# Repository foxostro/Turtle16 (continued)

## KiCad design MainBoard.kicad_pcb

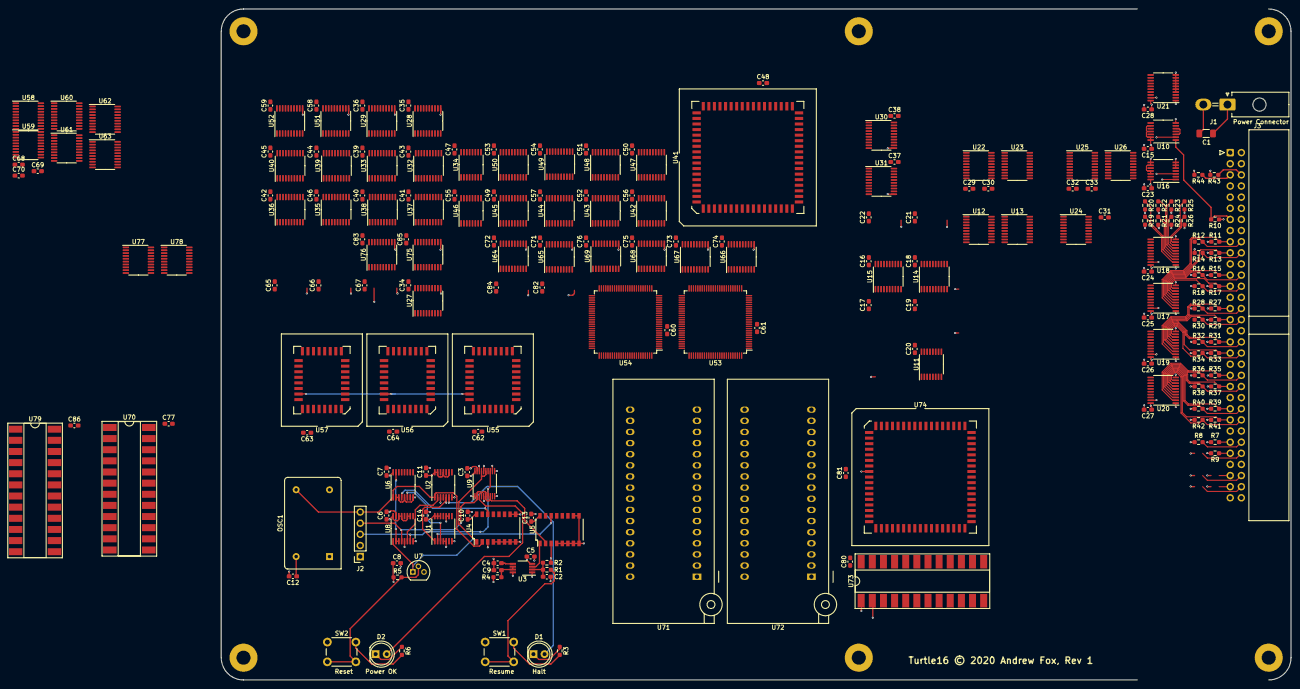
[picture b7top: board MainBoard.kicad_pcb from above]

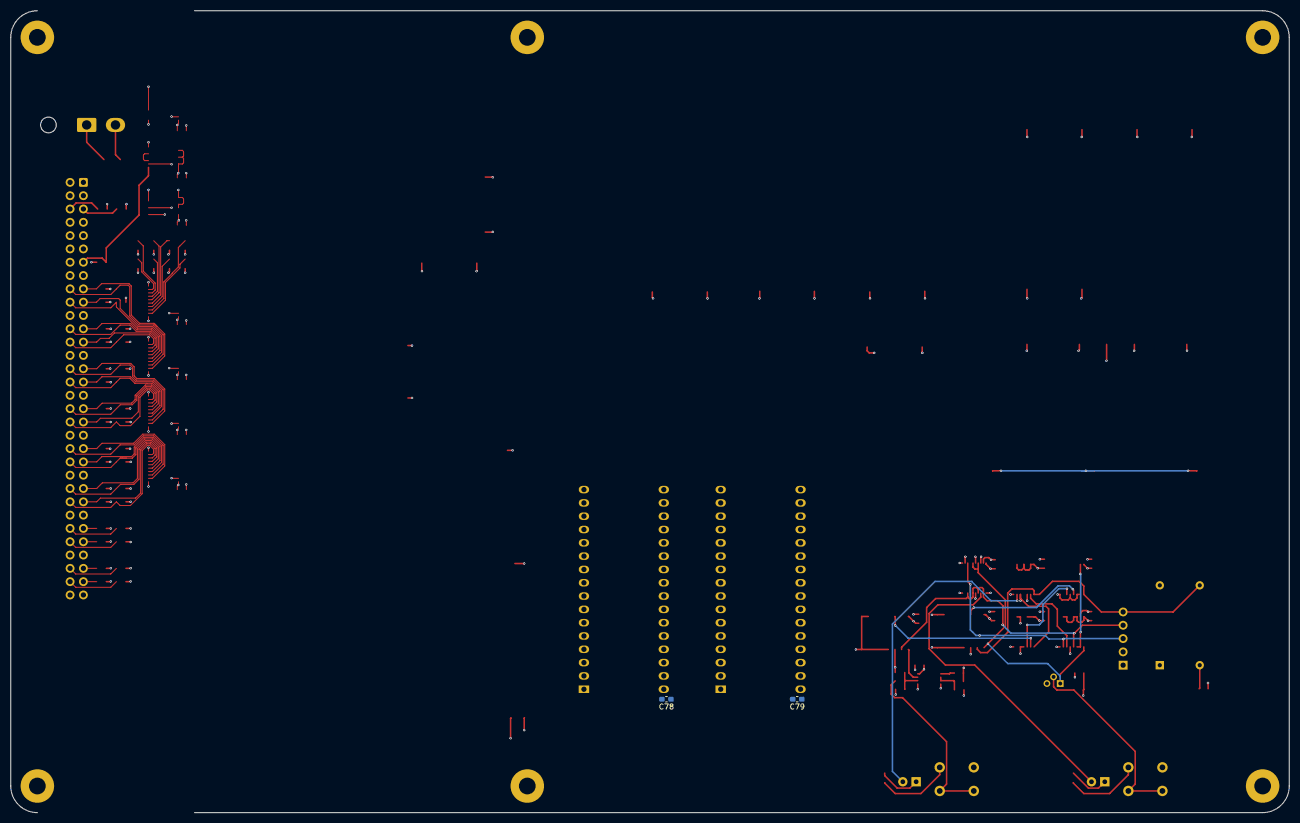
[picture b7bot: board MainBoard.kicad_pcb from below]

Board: 6 copper layers, 244.0 x 153.0 mm, 223 parts (2 on the bottom side), 442 nets.

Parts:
C1: 100µF; C_1206_3216Metric_Pad1.33x1.80mm_HandSolder
C2: 10uF; C_0603_1608Metric_Pad1.08x0.95mm_HandSolder
C3, C5, C6, C7, C8, C10, C11, C12, C13, C14, C15, C16, C17, C18, C19, C20, C21, C22, C23, C24, C25, C26, C27, C28, C29, C30, C31, C32, C33, C34, C35, C36, C37, C38, C39, C40, C41, C42, C43, C44, C45, C46, C47, C48, C49, C50, C51, C52, C53, C54, C55, C56, C57, C58, C59, C60, C61, C62, C63, C64, C65, C66, C67, C68, C69, C70, C71, C72, C73, C74, C75, C76, C77, C78, C79, C80, C81, C82, C83, C84, C85, C86: 100nF; C_0603_1608Metric_Pad1.08x0.95mm_HandSolder
C4: 0.01uF; C_0603_1608Metric_Pad1.08x0.95mm_HandSolder
C9: 22pF; C_0603_1608Metric_Pad1.08x0.95mm_HandSolder
D1: Halt; LED_D5.0mm
D2: Power OK; LED_D5.0mm
H1, H2, H3, H4, H5, H6: MountingHole_Pad; MountingHole_3.2mm_M3_Pad
J1: Power Connector; Molex_Mini-Fit_Jr_5569-02A2_2x01_P4.20mm_Horizontal
J2: External Clock; PinSocket_1x05_P2.54mm_Vertical
J3: 71922-264LF; IDC-Header_2x32_P2.54mm_Horizontal
OSC1: 12MHz; Oscillator_DIP-14
R1, R4, R5: 1kΩ; R_0603_1608Metric_Pad0.98x0.95mm_HandSolder
R2, R7, R8, R9, R10, R11, R12, R13, R14, R15, R16, R17, R18, R19, R20, R21, R22, R23, R24, R25, R26, R27, R28, R29, R30, R31, R32, R33, R34, R35, R36, R37, R38, R39, R40, R41, R42, R43, R44: 10kΩ; R_0603_1608Metric_Pad0.98x0.95mm_HandSolder
R3, R6: 220Ω; R_0603_1608Metric_Pad0.98x0.95mm_HandSolder
SW1: Resume; SW_PUSH_6mm_H5mm
SW2: Reset; SW_PUSH_6mm_H5mm
U1: 74AHCT32; TSSOP-14_4.4x5mm_P0.65mm
U2, U10: 74AHCT04; TSSOP-14_4.4x5mm_P0.65mm
U3: LM555; VSSOP-8_3.0x3.0mm_P0.65mm
U4, U5: 74F161; SOP-16_4.4x10.4mm_P1.27mm
U6, U11, U34, U46: 74AHCT138; TSSOP-16_4.4x5mm_P0.65mm
U7: MCP100-450D; TO-92
U8: 74AHCT157; TSSOP-16_4.4x5mm_P0.65mm
U9: 74AHCT244; TSSOP-20_4.4x5mm_P0.5mm
U12, U13, U14, U15, U32, U33, U35, U36, U37, U38, U39, U40, U42, U43, U44, U45, U47, U48, U49, U50: 74ABT245; TSSOP-20_4.4x6.5mm_P0.65mm
U16: 74AHCT02; TSSOP-14_4.4x5mm_P0.65mm
U17, U18, U19, U20, U21: 74AHCT245; TSSOP-20_4.4x6.5mm_P0.65mm
U22, U23, U24, U25, U26: 74ABT574; TSSOP-20_4.4x6.5mm_P0.65mm
U27: 74ABT377; TSSOP-20_4.4x6.5mm_P0.65mm
U28, U29, U30, U31, U51, U52, U64, U65, U66, U67, U68, U69, U75, U76: 74AHCT574; TSSOP-20_4.4x6.5mm_P0.65mm
U41, U74: IDT7381; PLCC-68_SMD-Socket
U53, U54: IDT7024L15PFG; TQFP-100_14x14mm_P0.5mm
U55, U56, U57: SST39SF010A-45-4I-NHE; PLCC-32_SMD-Socket
U58, U59, U60, U77, U78: 74AHCT273; TSSOP-20_4.4x6.5mm_P0.65mm
U61, U62, U63: 74AHCT240; TSSOP-20_4.4x6.5mm_P0.65mm
U70, U73, U79: ATF22V10C-7PX; DIP-24_W8.89mm_SMDSocket_LongPads
U71, U72: SST39SF010A-45-4I-NHE; DIP_Socket-32_W11.9_W12.7_W15.24_W17.78_W18.5_3M_232-1285-0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

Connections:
/Clock/Phi1: J2.4, U5.2, U8.4, U9.2, U9.4, U9.6, U9.8
/Clock/RawClockSignal: J2.5, OSC1.8, U2.1, U4.2, U6.1
/Clock/~HLT: U1.1, U2.5, U61.18
/Clock/~RDY: U4.3, U10.2, U16.3, U19.19, U20.19, U21.19
/EX/ALU/C16: U27.3, U41.20
/EX/ALU/OVF: U27.7, U41.24
/EX/ALU/RightOp0: U41.53, U42.18, U44.18, U47.18, U49.18
/EX/ALU/RightOp1: U41.54, U42.17, U44.17, U47.17, U49.17
/EX/ALU/RightOp2: U41.55, U42.16, U44.16, U47.16, U49.16
/EX/ALU/RightOp3: U41.56, U42.15, U44.15, U47.15, U49.15
/EX/ALU/RightOp4: U41.57, U42.14, U44.14, U47.14, U49.14
/EX/ALU/RightOp5: U41.58, U42.13, U44.13, U47.13, U49.13
/EX/ALU/RightOp6: U41.59, U42.12, U44.12, U47.12, U49.12
/EX/ALU/RightOp7: U41.60, U42.11, U44.11, U47.11, U49.11
/EX/ALU/RightOp8: U41.61, U43.18, U45.18, U48.18, U50.18
/EX/ALU/RightOp9: U41.62, U43.17, U45.17, U48.17, U50.17
/EX/ALU/RightOp10: U41.63, U43.16, U45.16, U48.16, U50.16
/EX/ALU/RightOp11: U41.64, U43.15, U45.15, U48.15, U50.15
/EX/ALU/RightOp12: U41.65, U43.14, U45.14, U48.14, U50.14
/EX/ALU/RightOp13: U41.66, U43.13, U45.13, U48.13, U50.13
/EX/ALU/RightOp14: U41.67, U43.12, U45.12, U48.12, U50.12
/EX/ALU/RightOp15: U41.68, U43.11, U45.11, U48.11, U50.11
/EX/ALU/Y_EX0: U30.2, U41.43, U74.53
/EX/ALU/Y_EX1: U30.3, U41.42, U74.54
/EX/ALU/Y_EX2: U30.4, U41.41, U74.55
/EX/ALU/Y_EX3: U30.5, U41.40, U74.56
/EX/ALU/Y_EX4: U30.6, U41.39, U74.57
/EX/ALU/Y_EX5: U30.7, U41.38, U74.58
/EX/ALU/Y_EX6: U30.8, U41.37, U74.59
/EX/ALU/Y_EX7: U30.9, U41.36, U74.60
/EX/ALU/Y_EX8: U31.2, U41.35, U74.61
/EX/ALU/Y_EX9: U31.3, U41.34, U74.62
/EX/ALU/Y_EX10: U31.4, U41.33, U74.63
/EX/ALU/Y_EX11: U31.5, U41.32, U74.64
/EX/ALU/Y_EX12: U31.6, U41.31, U74.65
/EX/ALU/Y_EX13: U31.7, U41.30, U74.66
/EX/ALU/Y_EX14: U31.8, U41.29, U74.67
/EX/ALU/Y_EX15: U31.9, U41.28, U74.68
/EX/ALU/Z: U27.4, U41.23
/EX/Carry: U27.2, U55.7, U56.7, U57.7
/EX/Ctl_EX1: U34.1, U61.16
/EX/Ctl_EX2: U34.2, U61.14
/EX/Ctl_EX3: U46.1, U61.12
/EX/Ctl_EX4: U46.2, U61.9
/EX/Ctl_EX5: U27.1, U61.7, U70.2
/EX/Ctl_EX6: U41.44, U61.5
/EX/Ctl_EX7: U41.45, U61.3
/EX/Ctl_EX8: U41.46, U62.18
/EX/Ctl_EX9: U41.47, U62.16
/EX/Ctl_EX10: U41.48, U62.14
/EX/Ctl_EX11: U41.49, U62.12
/EX/OVF: U27.6, U55.5, U56.5, U57.5
/EX/Select Right Operand/B0: U32.2, U42.2, U68.19
/EX/Select Right Operand/B1: U32.3, U42.3, U68.18
/EX/Select Right Operand/B2: U32.4, U42.4, U68.17
/EX/Select Right Operand/B3: U32.5, U42.5, U68.16
/EX/Select Right Operand/B4: U32.6, U42.6, U68.15
/EX/Select Right Operand/B5: U32.7, U42.7, U68.14
/EX/Select Right Operand/B6: U32.8, U42.8, U68.13
/EX/Select Right Operand/B7: U32.9, U42.9, U68.12
/EX/Select Right Operand/B8: U33.2, U35.2, U43.2, U69.19
/EX/Select Right Operand/B9: U33.3, U35.3, U43.3, U69.18
/EX/Select Right Operand/B10: U33.4, U35.4, U43.4, U69.17
/EX/Select Right Operand/B11: U33.5, U35.5, U43.5, U69.16
/EX/Select Right Operand/B12: U33.6, U35.6, U43.6, U69.15
/EX/Select Right Operand/B13: U33.7, U35.7, U43.7, U69.14
/EX/Select Right Operand/B14: U33.8, U35.8, U43.8, U69.13
/EX/Select Right Operand/B15: U33.9, U35.9, U43.9, U69.12
/EX/Select Right Operand/Ins_EX0: U39.2, U44.2, U47.2, U49.2, U64.19
/EX/Select Right Operand/Ins_EX1: U39.3, U44.3, U47.3, U49.3, U64.18
/EX/Select Right Operand/Ins_EX2: U39.4, U44.4, U49.4, U64.17
/EX/Select Right Operand/Ins_EX3: U39.5, U44.5, U49.5, U64.16
/EX/Select Right Operand/Ins_EX4: U39.6, U44.6, U44.7, U44.8, U44.9, U45.2, U45.3, U45.4, U45.5, U45.6, U45.7, U45.8, U45.9, U49.6, U64.15
/EX/Select Right Operand/Ins_EX8: U29.2, U47.4, U49.7, U65.19, U70.18
/EX/Select Right Operand/Ins_EX9: U29.3, U47.5, U49.8, U65.18, U70.17
/EX/Select Right Operand/Ins_EX10: U29.4, U47.6, U47.7, U47.8, U47.9, U48.2, U48.3, U48.4, U48.5, U48.6, U48.7, U48.8, U48.9, U49.9, U50.2, U50.3, U50.4, U50.5, U50.6, U50.7, U50.8, U50.9, U65.17, U70.16
/EX/Z: U27.5, U55.6, U56.6, U57.6
/EX/sheet5FD8D6EA/StoreOp_EX0: U32.18, U35.18, U37.18, U39.18, U51.2
/EX/sheet5FD8D6EA/StoreOp_EX1: U32.17, U35.17, U37.17, U39.17, U51.3
/EX/sheet5FD8D6EA/StoreOp_EX2: U32.16, U35.16, U37.16, U39.16, U51.4
/EX/sheet5FD8D6EA/StoreOp_EX3: U32.15, U35.15, U37.15, U39.15, U51.5
/EX/sheet5FD8D6EA/StoreOp_EX4: U32.14, U35.14, U37.14, U39.14, U51.6
/EX/sheet5FD8D6EA/StoreOp_EX5: U32.13, U35.13, U37.13, U39.13, U51.7
/EX/sheet5FD8D6EA/StoreOp_EX6: U32.12, U35.12, U37.12, U39.12, U51.8
/EX/sheet5FD8D6EA/StoreOp_EX7: U32.11, U35.11, U37.11, U39.11, U51.9
/EX/sheet5FD8D6EA/StoreOp_EX8: U33.18, U36.18, U38.18, U40.18, U52.2
/EX/sheet5FD8D6EA/StoreOp_EX9: U33.17, U36.17, U38.17, U40.17, U52.3
/EX/sheet5FD8D6EA/StoreOp_EX10: U33.16, U36.16, U38.16, U40.16, U52.4
/EX/sheet5FD8D6EA/StoreOp_EX11: U33.15, U36.15, U38.15, U40.15, U52.5
/EX/sheet5FD8D6EA/StoreOp_EX12: U33.14, U36.14, U38.14, U40.14, U52.6
/EX/sheet5FD8D6EA/StoreOp_EX13: U33.13, U36.13, U38.13, U40.13, U52.7
/EX/sheet5FD8D6EA/StoreOp_EX14: U33.12, U36.12, U38.12, U40.12, U52.8
/EX/sheet5FD8D6EA/StoreOp_EX15: U33.11, U36.11, U38.11, U40.11, U52.9
/EX/sheet5FD8D6EA/StoreOp_MEM0: U17.18, U51.19
/EX/sheet5FD8D6EA/StoreOp_MEM1: U17.17, U51.18
/EX/sheet5FD8D6EA/StoreOp_MEM2: U17.16, U51.17
/EX/sheet5FD8D6EA/StoreOp_MEM3: U17.15, U51.16
/EX/sheet5FD8D6EA/StoreOp_MEM4: U17.14, U51.15
/EX/sheet5FD8D6EA/StoreOp_MEM5: U17.13, U51.14
/EX/sheet5FD8D6EA/StoreOp_MEM6: U17.12, U51.13
/EX/sheet5FD8D6EA/StoreOp_MEM7: U17.11, U51.12
/EX/sheet5FD8D6EA/StoreOp_MEM8: U18.18, U52.19
/EX/sheet5FD8D6EA/StoreOp_MEM9: U18.17, U52.18
/EX/sheet5FD8D6EA/StoreOp_MEM10: U18.16, U52.17
/EX/sheet5FD8D6EA/StoreOp_MEM11: U18.15, U52.16
/EX/sheet5FD8D6EA/StoreOp_MEM12: U18.14, U52.15
/EX/sheet5FD8D6EA/StoreOp_MEM13: U18.13, U52.14
/EX/sheet5FD8D6EA/StoreOp_MEM14: U18.12, U52.13
/EX/sheet5FD8D6EA/StoreOp_MEM15: U18.11, U52.12
/EX/sheet5FD8D6EB/Ctl_EX14: U28.2, U62.5
/EX/sheet5FD8D6EB/Ctl_EX15: U28.3, U62.3
/EX/sheet5FD8D6EB/Ctl_EX16: U28.4, U63.18
/EX/sheet5FD8D6EB/Ctl_EX17: U28.5, U63.16
/EX/sheet5FD8D6EB/Ctl_EX18: U28.6, U63.14
/EX/sheet5FD8D6EB/Ctl_EX19: U28.7, U63.12
/EX/sheet5FD8D6EB/Ctl_EX20: U28.8, U63.9, U70.3
/EX/sheet5FD8D6EB/Ctl_MEM17: U24.2, U28.16
/EX/sheet5FD8D6EB/Ctl_MEM18: U24.3, U28.15
/EX/sheet5FD8D6EB/Ctl_MEM19: U24.4, U28.14
/EX/sheet5FD8D6EB/Ctl_MEM20: U24.5, U28.13, U70.4
/EX/sheet5FD8D6EB/SelC_MEM0: U24.7, U29.19, U70.15
/EX/sheet5FD8D6EB/SelC_MEM1: U24.8, U29.18, U70.14
/EX/sheet5FD8D6EB/SelC_MEM2: U24.9, U29.17, U70.13
/EX/sheet5FD8D6EC/Y_MEM0: U19.18, U25.2, U30.19
/EX/sheet5FD8D6EC/Y_MEM1: U19.17, U25.3, U30.18
/EX/sheet5FD8D6EC/Y_MEM2: U19.16, U25.4, U30.17
/EX/sheet5FD8D6EC/Y_MEM3: U19.15, U25.5, U30.16
/EX/sheet5FD8D6EC/Y_MEM4: U19.14, U25.6, U30.15
/EX/sheet5FD8D6EC/Y_MEM5: U19.13, U25.7, U30.14
/EX/sheet5FD8D6EC/Y_MEM6: U19.12, U25.8, U30.13
/EX/sheet5FD8D6EC/Y_MEM7: U19.11, U25.9, U30.12
/EX/sheet5FD8D6EC/Y_MEM8: U20.18, U26.2, U31.19
/EX/sheet5FD8D6EC/Y_MEM9: U20.17, U26.3, U31.18
/EX/sheet5FD8D6EC/Y_MEM10: U20.16, U26.4, U31.17
/EX/sheet5FD8D6EC/Y_MEM11: U20.15, U26.5, U31.16
/EX/sheet5FD8D6EC/Y_MEM12: U20.14, U26.6, U31.15
/EX/sheet5FD8D6EC/Y_MEM13: U20.13, U26.7, U31.14
/EX/sheet5FD8D6EC/Y_MEM14: U20.12, U26.8, U31.13
/EX/sheet5FD8D6EC/Y_MEM15: U20.11, U26.9, U31.12
/EX/sheet5FDDE432/Ins_EX5: U39.7, U64.14
/EX/sheet5FDDE432/Ins_EX6: U39.8, U64.13
/EX/sheet5FDDE432/Ins_EX7: U39.9, U40.2, U40.3, U40.4, U40.5, U40.6, U40.7, U40.8, U40.9, U64.12
/EX/sheet5FDDE432/PC_EX0: U37.2, U75.19
/EX/sheet5FDDE432/PC_EX1: U37.3, U75.18
/EX/sheet5FDDE432/PC_EX2: U37.4, U75.17
/EX/sheet5FDDE432/PC_EX3: U37.5, U75.16
/EX/sheet5FDDE432/PC_EX4: U37.6, U75.15
/EX/sheet5FDDE432/PC_EX5: U37.7, U75.14
/EX/sheet5FDDE432/PC_EX6: U37.8, U75.13
/EX/sheet5FDDE432/PC_EX7: U37.9, U75.12
/EX/sheet5FDDE432/PC_EX8: U38.2, U76.19
/EX/sheet5FDDE432/PC_EX9: U38.3, U76.18
/EX/sheet5FDDE432/PC_EX10: U38.4, U76.17
/EX/sheet5FDDE432/PC_EX11: U38.5, U76.16
/EX/sheet5FDDE432/PC_EX12: U38.6, U76.15
/EX/sheet5FDDE432/PC_EX13: U38.7, U76.14
/EX/sheet5FDDE432/PC_EX14: U38.8, U76.13
/EX/sheet5FDDE432/PC_EX15: U38.9, U76.12
/EX/~J: U62.9, U70.11, U73.3
/EX/~JABS: U62.7, U73.4
/ID/Hazard Control/FlagsNeeded: U70.1, U79.23
/ID/Hazard Control/Ins_ID11: U55.12, U56.12, U57.12, U78.9, U79.1
/ID/Hazard Control/Ins_ID12: U55.11, U56.11, U57.11, U78.12, U79.2
/ID/Hazard Control/Ins_ID13: U55.10, U56.10, U57.10, U78.15, U79.3
/ID/Hazard Control/Ins_ID14: U55.9, U56.9, U57.9, U78.16, U79.4
/ID/Hazard Control/Ins_ID15: U55.8, U56.8, U57.8, U78.19, U79.5
/ID/ID/EX A/A0: U41.1, U66.19
/ID/ID/EX A/A1: U41.2, U66.18
/ID/ID/EX A/A2: U41.3, U66.17
/ID/ID/EX A/A3: U41.4, U66.16
/ID/ID/EX A/A4: U41.5, U66.15
/ID/ID/EX A/A5: U41.6, U66.14
/ID/ID/EX A/A6: U41.7, U66.13
/ID/ID/EX A/A7: U41.8, U66.12
/ID/ID/EX A/A8: U41.9, U67.19
/ID/ID/EX A/A9: U41.10, U67.18
/ID/ID/EX A/A10: U41.11, U67.17
/ID/ID/EX A/A11: U41.12, U67.16
/ID/ID/EX A/A12: U41.13, U67.15
/ID/ID/EX A/A13: U41.14, U67.14
/ID/ID/EX A/A14: U41.15, U67.13
/ID/ID/EX A/A15: U41.16, U67.12
/ID/ID/EX ControlWord/Ctl_ID0: U55.13, U58.3
/ID/ID/EX ControlWord/Ctl_ID1: U55.14, U58.4
/ID/ID/EX ControlWord/Ctl_ID2: U55.15, U58.7
/ID/ID/EX ControlWord/Ctl_ID3: U55.17, U58.8
/ID/ID/EX ControlWord/Ctl_ID4: U55.18, U58.13
/ID/ID/EX ControlWord/Ctl_ID5: U55.19, U58.14
/ID/ID/EX ControlWord/Ctl_ID6: U55.20, U58.17
/ID/ID/EX ControlWord/Ctl_ID7: U55.21, U58.18
/ID/ID/EX ControlWord/Ctl_ID8: U56.13, U59.3
/ID/ID/EX ControlWord/Ctl_ID9: U56.14, U59.4
/ID/ID/EX ControlWord/Ctl_ID10: U56.15, U59.7
/ID/ID/EX ControlWord/Ctl_ID11: U56.17, U59.8
/ID/ID/EX ControlWord/Ctl_ID12: U56.18, U59.13
/ID/ID/EX ControlWord/Ctl_ID13: U56.19, U59.14
/ID/ID/EX ControlWord/Ctl_ID14: U56.20, U59.17
/ID/ID/EX ControlWord/Ctl_ID15: U56.21, U59.18
/ID/ID/EX ControlWord/Ctl_ID16: U57.13, U60.3
/ID/ID/EX ControlWord/Ctl_ID17: U57.14, U60.4
/ID/ID/EX ControlWord/Ctl_ID18: U57.15, U60.7
/ID/ID/EX ControlWord/Ctl_ID19: U57.17, U60.8
/ID/ID/EX ControlWord/Ctl_ID20: U57.18, U60.13
/ID/ID/EX ControlWord/Ctl_ID21: U57.19, U60.14
/ID/ID/EX ControlWord/Ctl_ID22: U57.20, U60.17
/ID/ID/EX ControlWord/Ctl_ID23: U57.21, U60.18
/ID/ID/EX InstructionWord/Ins_ID0: U64.2, U77.2
/ID/ID/EX InstructionWord/Ins_ID1: U64.3, U77.5
/ID/ID/EX InstructionWord/Ins_ID2: U54.59, U64.4, U70.8, U77.6
/ID/ID/EX InstructionWord/Ins_ID3: U54.58, U64.5, U70.9, U77.9
/ID/ID/EX InstructionWord/Ins_ID4: U54.57, U64.6, U70.10, U77.12
/ID/ID/EX InstructionWord/Ins_ID5: U53.59, U64.7, U70.5, U77.15
/ID/ID/EX InstructionWord/Ins_ID6: U53.58, U64.8, U70.6, U77.16
/ID/ID/EX InstructionWord/Ins_ID7: U53.57, U64.9, U70.7, U77.19
/ID/ID/EX InstructionWord/Ins_ID8: U65.2, U78.2
/ID/ID/EX InstructionWord/Ins_ID9: U65.3, U78.5
/ID/ID/EX InstructionWord/Ins_ID10: U65.4, U78.6
/ID/STALL_PC: U70.22, U74.25
/ID/sheet5FC16A8C/A0: U53.14, U66.2
/ID/sheet5FC16A8C/A1: U53.15, U66.3
/ID/sheet5FC16A8C/A2: U53.16, U66.4
/ID/sheet5FC16A8C/A3: U53.18, U66.5
/ID/sheet5FC16A8C/A4: U53.19, U66.6
/ID/sheet5FC16A8C/A5: U53.20, U66.7
/ID/sheet5FC16A8C/A6: U53.21, U66.8
/ID/sheet5FC16A8C/A7: U53.26, U66.9
/ID/sheet5FC16A8C/A8: U53.27, U67.2
/ID/sheet5FC16A8C/A9: U53.28, U67.3
/ID/sheet5FC16A8C/A10: U53.29, U67.4
/ID/sheet5FC16A8C/A11: U53.30, U67.5
/ID/sheet5FC16A8C/A12: U53.31, U67.6
/ID/sheet5FC16A8C/A13: U53.32, U67.7
/ID/sheet5FC16A8C/A14: U53.33, U67.8
/ID/sheet5FC16A8C/A15: U53.35, U67.9
/ID/sheet5FC16A8C/B0: U54.14, U68.2
/ID/sheet5FC16A8C/B1: U54.15, U68.3
/ID/sheet5FC16A8C/B2: U54.16, U68.4
/ID/sheet5FC16A8C/B3: U54.18, U68.5
/ID/sheet5FC16A8C/B4: U54.19, U68.6
/ID/sheet5FC16A8C/B5: U54.20, U68.7
/ID/sheet5FC16A8C/B6: U54.21, U68.8
/ID/sheet5FC16A8C/B7: U54.26, U68.9
/ID/sheet5FC16A8C/B8: U54.27, U69.2
/ID/sheet5FC16A8C/B9: U54.28, U69.3
/ID/sheet5FC16A8C/B10: U54.29, U69.4
/ID/sheet5FC16A8C/B11: U54.30, U69.5
/ID/sheet5FC16A8C/B12: U54.31, U69.6
/ID/sheet5FC16A8C/B13: U54.32, U69.7
/ID/sheet5FC16A8C/B14: U54.33, U69.8
/ID/sheet5FC16A8C/B15: U54.35, U69.9
/ID/sheet5FC16A8C/C0: U12.18, U14.18, U53.90, U54.90
/ID/sheet5FC16A8C/C1: U12.17, U14.17, U53.91, U54.91
/ID/sheet5FC16A8C/C2: U12.16, U14.16, U53.93, U54.93
/ID/sheet5FC16A8C/C3: U12.15, U14.15, U53.94, U54.94
/ID/sheet5FC16A8C/C4: U12.14, U14.14, U53.95, U54.95
/ID/sheet5FC16A8C/C5: U12.13, U14.13, U53.96, U54.96
/ID/sheet5FC16A8C/C6: U12.12, U14.12, U53.97, U54.97
/ID/sheet5FC16A8C/C7: U12.11, U14.11, U53.98, U54.98
/ID/sheet5FC16A8C/C8: U13.18, U15.18, U53.99, U54.99
/ID/sheet5FC16A8C/C9: U13.17, U15.17, U53.100, U54.100
/ID/sheet5FC16A8C/C10: U13.16, U15.16, U53.5, U54.5
/ID/sheet5FC16A8C/C11: U13.15, U15.15, U53.6, U54.6
/ID/sheet5FC16A8C/C12: U13.14, U15.14, U53.7, U54.7
/ID/sheet5FC16A8C/C13: U13.13, U15.13, U53.8, U54.8
/ID/sheet5FC16A8C/C14: U13.12, U15.12, U53.10, U54.10
/ID/sheet5FC16A8C/C15: U13.11, U15.11, U53.11, U54.11
/ID/sheet5FC16A8C/SelC_WB0: U24.14, U53.66, U54.66
/ID/sheet5FC16A8C/SelC_WB1: U24.13, U53.67, U54.67
/ID/sheet5FC16A8C/SelC_WB2: U24.12, U53.68, U54.68
/ID/~STALL_ID: U58.1, U59.1, U60.1, U70.23
/ID/~STALL_IF: U70.21, U77.1, U78.1
/ID/~WBEN: U24.16, U53.87, U54.87
/ID/~WRH: U24.17, U53.84, U54.84
/ID/~WRL: U24.18, U53.83, U54.83
/IF/Instruction Memory/Ins_IF0: U71.13, U77.3
/IF/Instruction Memory/Ins_IF1: U71.14, U77.4
/IF/Instruction Memory/Ins_IF2: U71.15, U77.7
/IF/Instruction Memory/Ins_IF3: U71.17, U77.8
/IF/Instruction Memory/Ins_IF4: U71.18, U77.13
/IF/Instruction Memory/Ins_IF5: U71.19, U77.14
/IF/Instruction Memory/Ins_IF6: U71.20, U77.17
/IF/Instruction Memory/Ins_IF7: U71.21, U77.18
/IF/Instruction Memory/Ins_IF8: U72.13, U78.3
/IF/Instruction Memory/Ins_IF9: U72.14, U78.4
/IF/Instruction Memory/Ins_IF10: U72.15, U78.7
/IF/Instruction Memory/Ins_IF11: U72.17, U78.8
/IF/Instruction Memory/Ins_IF12: U72.18, U78.13
/IF/Instruction Memory/Ins_IF13: U72.19, U78.14
/IF/Instruction Memory/Ins_IF14: U72.20, U78.17
/IF/Instruction Memory/Ins_IF15: U72.21, U78.18
/IF/Instruction Memory/PC0: U71.12, U72.12, U74.1, U74.43, U75.2
/IF/Instruction Memory/PC1: U71.11, U72.11, U74.2, U74.42, U75.3
/IF/Instruction Memory/PC2: U71.10, U72.10, U74.3, U74.41, U75.4
/IF/Instruction Memory/PC3: U71.9, U72.9, U74.4, U74.40, U75.5
/IF/Instruction Memory/PC4: U71.8, U72.8, U74.5, U74.39, U75.6
/IF/Instruction Memory/PC5: U71.7, U72.7, U74.6, U74.38, U75.7
/IF/Instruction Memory/PC6: U71.6, U72.6, U74.7, U74.37, U75.8
/IF/Instruction Memory/PC7: U71.5, U72.5, U74.8, U74.36, U75.9
/IF/Instruction Memory/PC8: U71.27, U72.27, U74.9, U74.35, U76.2
/IF/Instruction Memory/PC9: U71.26, U72.26, U74.10, U74.34, U76.3
/IF/Instruction Memory/PC10: U71.23, U72.23, U74.11, U74.33, U76.4
/IF/Instruction Memory/PC11: U71.25, U72.25, U74.12, U74.32, U76.5
/IF/Instruction Memory/PC12: U71.4, U72.4, U74.13, U74.31, U76.6
/IF/Instruction Memory/PC13: U71.28, U72.28, U74.14, U74.30, U76.7
/IF/Instruction Memory/PC14: U71.29, U72.29, U74.15, U74.29, U76.8
/IF/Instruction Memory/PC15: U71.3, U72.3, U74.16, U74.28, U76.9
/MEM/Ctl_MEM14: U21.3, U28.19
/MEM/Ctl_MEM15: U21.2, U28.18
/MEM/Ctl_MEM16: U16.2, U28.17
/MEM/Sheet5FD9EFDA/Y_WB0: U12.2, U25.19
/MEM/Sheet5FD9EFDA/Y_WB1: U12.3, U25.18
/MEM/Sheet5FD9EFDA/Y_WB2: U12.4, U25.17
/MEM/Sheet5FD9EFDA/Y_WB3: U12.5, U25.16
/MEM/Sheet5FD9EFDA/Y_WB4: U12.6, U25.15
/MEM/Sheet5FD9EFDA/Y_WB5: U12.7, U25.14
/MEM/Sheet5FD9EFDA/Y_WB6: U12.8, U25.13
/MEM/Sheet5FD9EFDA/Y_WB7: U12.9, U25.12
/MEM/Sheet5FD9EFDA/Y_WB8: U13.2, U26.19
/MEM/Sheet5FD9EFDA/Y_WB9: U13.3, U26.18
/MEM/Sheet5FD9EFDA/Y_WB10: U13.4, U26.17
/MEM/Sheet5FD9EFDA/Y_WB11: U13.5, U26.16
/MEM/Sheet5FD9EFDA/Y_WB12: U13.6, U26.15
/MEM/Sheet5FD9EFDA/Y_WB13: U13.7, U26.14
/MEM/Sheet5FD9EFDA/Y_WB14: U13.8, U26.13
/MEM/Sheet5FD9EFDA/Y_WB15: U13.9, U26.12
/MEM/sheet5FD56BF4/StoreOp_WB0: U14.2, U22.19
/MEM/sheet5FD56BF4/StoreOp_WB1: U14.3, U22.18
/MEM/sheet5FD56BF4/StoreOp_WB2: U14.4, U22.17
/MEM/sheet5FD56BF4/StoreOp_WB3: U14.5, U22.16
/MEM/sheet5FD56BF4/StoreOp_WB4: U14.6, U22.15
/MEM/sheet5FD56BF4/StoreOp_WB5: U14.7, U22.14
/MEM/sheet5FD56BF4/StoreOp_WB6: U14.8, U22.13
/MEM/sheet5FD56BF4/StoreOp_WB7: U14.9, U22.12
/MEM/sheet5FD56BF4/StoreOp_WB8: U15.2, U23.19
/MEM/sheet5FD56BF4/StoreOp_WB9: U15.3, U23.18
/MEM/sheet5FD56BF4/StoreOp_WB10: U15.4, U23.17
/MEM/sheet5FD56BF4/StoreOp_WB11: U15.5, U23.16
/MEM/sheet5FD56BF4/StoreOp_WB12: U15.6, U23.15
/MEM/sheet5FD56BF4/StoreOp_WB13: U15.7, U23.14
/MEM/sheet5FD56BF4/StoreOp_WB14: U15.8, U23.13
/MEM/sheet5FD56BF4/StoreOp_WB15: U15.9, U23.12
/MEM/~MemLoad: J3.4, R44.1, U21.17
/MEM/~MemStore: J3.3, R43.1, U21.18
/System Bus Connector/Addr0: J3.37, R27.1, U19.2
/System Bus Connector/Addr1: J3.38, R28.1, U19.3
/System Bus Connector/Addr2: J3.39, R29.1, U19.4
/System Bus Connector/Addr3: J3.40, R30.1, U19.5
/System Bus Connector/Addr4: J3.43, R31.1, U19.6
/System Bus Connector/Addr5: J3.44, R32.1, U19.7
/System Bus Connector/Addr6: J3.45, R33.1, U19.8
/System Bus Connector/Addr7: J3.46, R34.1, U19.9
/System Bus Connector/Addr8: J3.49, R35.1, U20.2
/System Bus Connector/Addr9: J3.50, R36.1, U20.3
/System Bus Connector/Addr10: J3.51, R37.1, U20.4
/System Bus Connector/Addr11: J3.52, R38.1, U20.5
/System Bus Connector/Addr12: J3.55, R39.1, U20.6
/System Bus Connector/Addr13: J3.56, R40.1, U20.7
/System Bus Connector/Addr14: J3.57, R41.1, U20.8
/System Bus Connector/Addr15: J3.58, R42.1, U20.9
/System Bus Connector/Bank0: J3.10, R7.1
/System Bus Connector/Bank1: J3.61, R8.1
/System Bus Connector/Bank2: J3.62, R9.1
/System Bus Connector/IO0: J3.13, R11.1, U17.2, U22.2
/System Bus Connector/IO1: J3.14, R12.1, U17.3, U22.3
/System Bus Connector/IO2: J3.15, R13.1, U17.4, U22.4
/System Bus Connector/IO3: J3.16, R14.1, U17.5, U22.5
/System Bus Connector/IO4: J3.19, R15.1, U17.6, U22.6
/System Bus Connector/IO5: J3.20, R16.1, U17.7, U22.7
/System Bus Connector/IO6: J3.21, R17.1, U17.8, U22.8
/System Bus Connector/IO7: J3.22, R18.1, U17.9, U22.9
/System Bus Connector/IO8: J3.25, R19.1, U18.2, U23.2
/System Bus Connector/IO9: J3.26, R20.1, U18.3, U23.3
/System Bus Connector/IO10: J3.27, R21.1, U18.4, U23.4
/System Bus Connector/IO11: J3.28, R22.1, U18.5, U23.5
/System Bus Connector/IO12: J3.31, R23.1, U18.6, U23.6
/System Bus Connector/IO13: J3.32, R24.1, U18.7, U23.7
/System Bus Connector/IO14: J3.33, R25.1, U18.8, U23.8
/System Bus Connector/IO15: J3.34, R26.1, U18.9, U23.9
/System Bus Connector/RDY: J3.5, R10.2, U10.1
/WB/Ctl_WB17: U11.1, U24.19
GND: C1.2, C2.2, C3.2, C4.2, C5.2, C6.2, C7.2, C8.2, C9.2, C10.2, C11.2, C12.2, C13.2, C14.2, C15.2, C16.2, C17.2, C18.2, C19.2, C20.2, C21.2, C22.2, C23.2, C24.2, C25.2, C26.2, C27.2, C28.2, C29.2, C30.2, C31.2, C32.2, C33.2, C34.2, C35.2, C36.2, C37.2, C38.2, C39.2, C40.2, C41.2, C42.2, C43.2, C44.2, C45.2, C46.2, C47.2, C48.2, C49.2, C50.2, C51.2, C52.2, C53.2, C54.2, C55.2, C56.2, C57.2, C58.2, C59.2, C60.2, C61.2, C62.2, C63.2, C64.2, C65.2, C66.2, C67.2, C68.2, C69.2, C70.2, C71.2, C72.2, C73.2, C74.2, C75.2, C76.2, C77.2, C78.2, C79.2, C80.2, C81.2, C82.2, C83.2, C84.2, C85.2, C86.2, H1.1, H2.1, H3.1, H4.1, H5.1, H6.1, J1.2, J2.1, J3.7, J3.8, J3.11, J3.12, J3.17, J3.18, J3.23, J3.24, J3.29, J3.30, J3.35, J3.36, J3.41, J3.42, J3.47, J3.48, J3.53, J3.54, J3.59, J3.60, J3.63, J3.64, OSC1.7, R3.2, R6.2, R7.2, R8.2, R9.2, R11.2, R12.2, R13.2, R14.2, R15.2, R16.2, R17.2, R18.2, R19.2, R20.2, R21.2, R22.2, R23.2, R24.2, R25.2, R26.2, R27.2, R28.2, R29.2, R30.2, R31.2, R32.2, R33.2, R34.2, R35.2, R36.2, R37.2, R38.2, R39.2, R40.2, R41.2, R42.2, R43.2, R44.2, SW1.1, SW2.1, U1.7, U2.7, U3.1, U4.4, U4.5, U4.6, U4.7, U4.8, U4.9, U4.10, U5.4, U5.5, U5.6, U5.7, U5.8, U5.9, U5.10, U6.2, U6.3, U6.5, U6.8, U7.3, U8.5, U8.8, U8.15, U9.1, U9.10, U9.19, U10.7, U11.2, U11.3, U11.4, U11.5, U11.8, U12.10, U13.10, U14.10, U15.10, U16.5, U16.6, U16.7, U16.8, U16.9, U16.11, U16.12, U17.1, U17.10, U18.1, U18.10, U19.1, U19.10, U20.1, U20.10, U21.4, U21.5, U21.6, U21.7, U21.8, U21.9, U21.10, U22.1, U22.10, U23.1, U23.10, U24.1, U24.10, U25.1, U25.10, U26.1, U26.10, U27.8, U27.10, U27.13, U27.14, U27.17, U27.18, U28.1, U28.10, U29.1, U29.10, U30.1, U30.10, U31.1, U31.10, U32.10, U33.10, U34.3, U34.4, U34.5, U34.8, U35.10, U36.2, U36.3, U36.4, U36.5, U36.6, U36.7, U36.8, U36.9, U36.10, U37.10, U38.10, U39.10, U40.10, U41.17, U41.19, U41.25, U41.27, U41.51, U41.52, U42.10, U43.10, U44.10, U45.10, U46.3, U46.4, U46.5, U46.8, U47.10, U48.10, U49.10, U50.10, U51.1, U51.10, U52.1, U52.10, U53.9, U53.13, U53.34, U53.36, U53.38, U53.39, U53.40, U53.41, U53.42, U53.44, U53.45, U53.46, U53.47, U53.48, U53.49, U53.50, U53.55, U53.56, U53.61, U53.62, U53.63, U53.64, U53.69, U53.70, U53.71, U53.76, U53.77, U53.78, U53.79, U53.80, U53.81, U53.85, U53.86, U53.89, U53.92, U54.9, U54.13, U54.34, U54.36, U54.38, U54.39, U54.40, U54.41, U54.42, U54.44, U54.45, U54.46, U54.47, U54.48, U54.49, U54.50, U54.55, U54.56, U54.61, U54.62, U54.63, U54.64, U54.69, U54.70, U54.71, U54.76, U54.77, U54.78, U54.79, U54.80, U54.81, U54.85, U54.86, U54.89, U54.92, U55.2, U55.3, U55.4, U55.16, U55.22, U55.23, U55.24, U55.25, U55.26, U55.28, U55.29, U56.2, U56.3, U56.4, U56.16, U56.22, U56.23, U56.24, U56.25, U56.26, U56.28, U56.29, U57.2, U57.3, U57.4, U57.16, U57.22, U57.23, U57.24, U57.25, U57.26, U57.28, U57.29, U58.10, U59.10, U60.10, U61.1, U61.10, U61.19, U62.1, U62.10, U62.19, U63.1, U63.10, U63.19, U64.1, U64.10, U65.1, U65.10, U66.1, U66.10, U67.1, U67.10, U68.1, U68.10, U69.1, U69.10, U70.12, U70.19, U70.20, U71.2, U71.16, U71.22, U71.24, U72.2, U72.16, U72.22, U72.24, U73.12, U73.13, U74.19, U74.27, U74.50, U74.51, U74.52, U75.1, U75.10, U76.1, U76.10, U77.10, U78.10, U79.12
unnamed: C2.1, R1.1, R2.2, U3.2
unnamed: C4.1, U3.5
unnamed: C9.1, R4.2, U3.6, U3.7
unnamed: D1.1, R3.1
unnamed: D1.2, U2.6
unnamed: D2.1, R6.1
unnamed: D2.2, U9.3
unnamed: J2.3, U8.7, U9.13
unnamed: R1.2, SW1.2
unnamed: R5.2, SW2.2, U7.2
unnamed: U1.2, U5.14
unnamed: U1.3, U6.6
unnamed: U2.2, U8.6
unnamed: U3.3, U5.1
unnamed: U4.1, U7.1, U8.1, U9.15, U9.17
unnamed: U4.14, U6.4
unnamed: U6.15, U8.2, U8.3
unnamed: U11.14, U14.19, U15.19
unnamed: U11.15, U12.19, U13.19
unnamed: U16.1, U17.19, U18.19
unnamed: U32.19, U33.19, U34.15
unnamed: U34.12, U39.19, U40.19
unnamed: U34.13, U37.19, U38.19
unnamed: U34.14, U35.19, U36.19
unnamed: U42.19, U43.19, U46.15
unnamed: U44.19, U45.19, U46.14
unnamed: U46.12, U49.19, U50.19
unnamed: U46.13, U47.19, U48.19
unnamed: U58.2, U61.2
unnamed: U58.5, U61.4
unnamed: U58.6, U61.6
unnamed: U58.9, U61.8
unnamed: U58.12, U61.11
unnamed: U58.15, U61.13
unnamed: U58.16, U61.15
unnamed: U58.19, U61.17
unnamed: U59.2, U62.2
unnamed: U59.5, U62.4
unnamed: U59.6, U62.6
unnamed: U59.9, U62.8
unnamed: U59.12, U62.11
unnamed: U59.15, U62.13
unnamed: U59.16, U62.15
unnamed: U59.19, U62.17
unnamed: U60.2, U63.2
unnamed: U60.5, U63.4
unnamed: U60.6, U63.6
unnamed: U60.9, U63.8
unnamed: U60.12, U63.11
unnamed: U73.18, U74.49
unnamed: U73.19, U74.48
unnamed: U73.20, U74.47
unnamed: U73.21, U74.46
unnamed: U73.22, U74.45
unnamed: U73.23, U74.44
Phi1a: U9.18, U27.11, U28.11, U29.11, U51.11, U52.11, U58.11, U59.11, U60.11
Phi1b: U9.16, U64.11, U65.11, U66.11, U67.11, U68.11, U69.11, U75.11, U76.11, U77.11, U78.11
Phi1c: U9.14, U22.11, U23.11, U24.11, U25.11, U26.11, U30.11, U31.11, U73.1, U74.17
Phi2: J3.9, U9.7
VCC: C1.1, C3.1, C5.1, C6.1, C7.1, C8.1, C10.1, C11.1, C12.1, C13.1, C14.1, C15.1, C16.1, C17.1, C18.1, C19.1, C20.1, C21.1, C22.1, C23.1, C24.1, C25.1, C26.1, C27.1, C28.1, C29.1, C30.1, C31.1, C32.1, C33.1, C34.1, C35.1, C36.1, C37.1, C38.1, C39.1, C40.1, C41.1, C42.1, C43.1, C44.1, C45.1, C46.1, C47.1, C48.1, C49.1, C50.1, C51.1, C52.1, C53.1, C54.1, C55.1, C56.1, C57.1, C58.1, C59.1, C60.1, C61.1, C62.1, C63.1, C64.1, C65.1, C66.1, C67.1, C68.1, C69.1, C70.1, C71.1, C72.1, C73.1, C74.1, C75.1, C76.1, C77.1, C78.1, C79.1, C80.1, C81.1, C82.1, C83.1, C84.1, C85.1, C86.1, J1.1, J2.2, J3.1, J3.2, OSC1.14, R2.1, R4.1, R5.1, R10.1, U1.4, U1.5, U1.9, U1.10, U1.12, U1.13, U1.14, U2.3, U2.9, U2.11, U2.13, U2.14, U3.4, U3.8, U4.16, U5.3, U5.16, U6.16, U8.10, U8.11, U8.13, U8.14, U8.16, U9.11, U9.20, U10.3, U10.5, U10.9, U10.11, U10.13, U10.14, U11.6, U11.16, U12.1, U12.20, U13.1, U13.20, U14.1, U14.20, U15.1, U15.20, U16.14, U17.20, U18.20, U19.20, U20.20, U21.1, U21.20, U22.20, U23.20, U24.6, U24.20, U25.20, U26.20, U27.20, U28.9, U28.20, U29.5, U29.6, U29.7, U29.8, U29.9, U29.20, U30.20, U31.20, U32.1, U32.20, U33.1, U33.20, U34.6, U34.16, U35.1, U35.20, U36.1, U36.20, U37.1, U37.20, U38.1, U38.20, U39.1, U39.20, U40.1, U40.20, U41.18, U41.26, U41.50, U42.1, U42.20, U43.1, U43.20, U44.1, U44.20, U45.1, U45.20, U46.6, U46.16, U47.1, U47.20, U48.1, U48.20, U49.1, U49.20, U50.1, U50.20, U51.20, U52.20, U53.12, U53.17, U53.37, U53.88, U54.12, U54.17, U54.37, U54.88, U55.31, U55.32, U56.31, U56.32, U57.31, U57.32, U58.20, U59.20, U60.20, U61.20, U62.20, U63.13, U63.15, U63.17, U63.20, U64.20, U65.5, U65.6, U65.7, U65.8, U65.9, U65.20, U66.20, U67.20, U68.20, U69.20, U70.24, U71.31, U71.32, U72.31, U72.32, U73.24, U74.18, U74.26, U75.20, U76.20, U77.20, U78.20, U79.24
~RST: J3.6, U9.5, U55.27, U56.27, U57.27, U73.2
